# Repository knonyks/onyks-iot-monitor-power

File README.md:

## ESP32 power meter

Based on:

* ACS712 - 30A
* 2ma - 2ma voltage measuring transformer
* ADS1115 - I2C ADC 16bit

Programer:

* [ESP-prog](https://docs.espressif.com/projects/esp-iot-solution/en/latest/hw-reference/ESP-Prog_guide.html)

### PCB V1:

* [schematic](img/V1/schematic_v1.pdf)
* [bom](fab/V1/ibom.html)
* PCB

### PCB V2:

---

Author: Maciej Załęski [macmysz]

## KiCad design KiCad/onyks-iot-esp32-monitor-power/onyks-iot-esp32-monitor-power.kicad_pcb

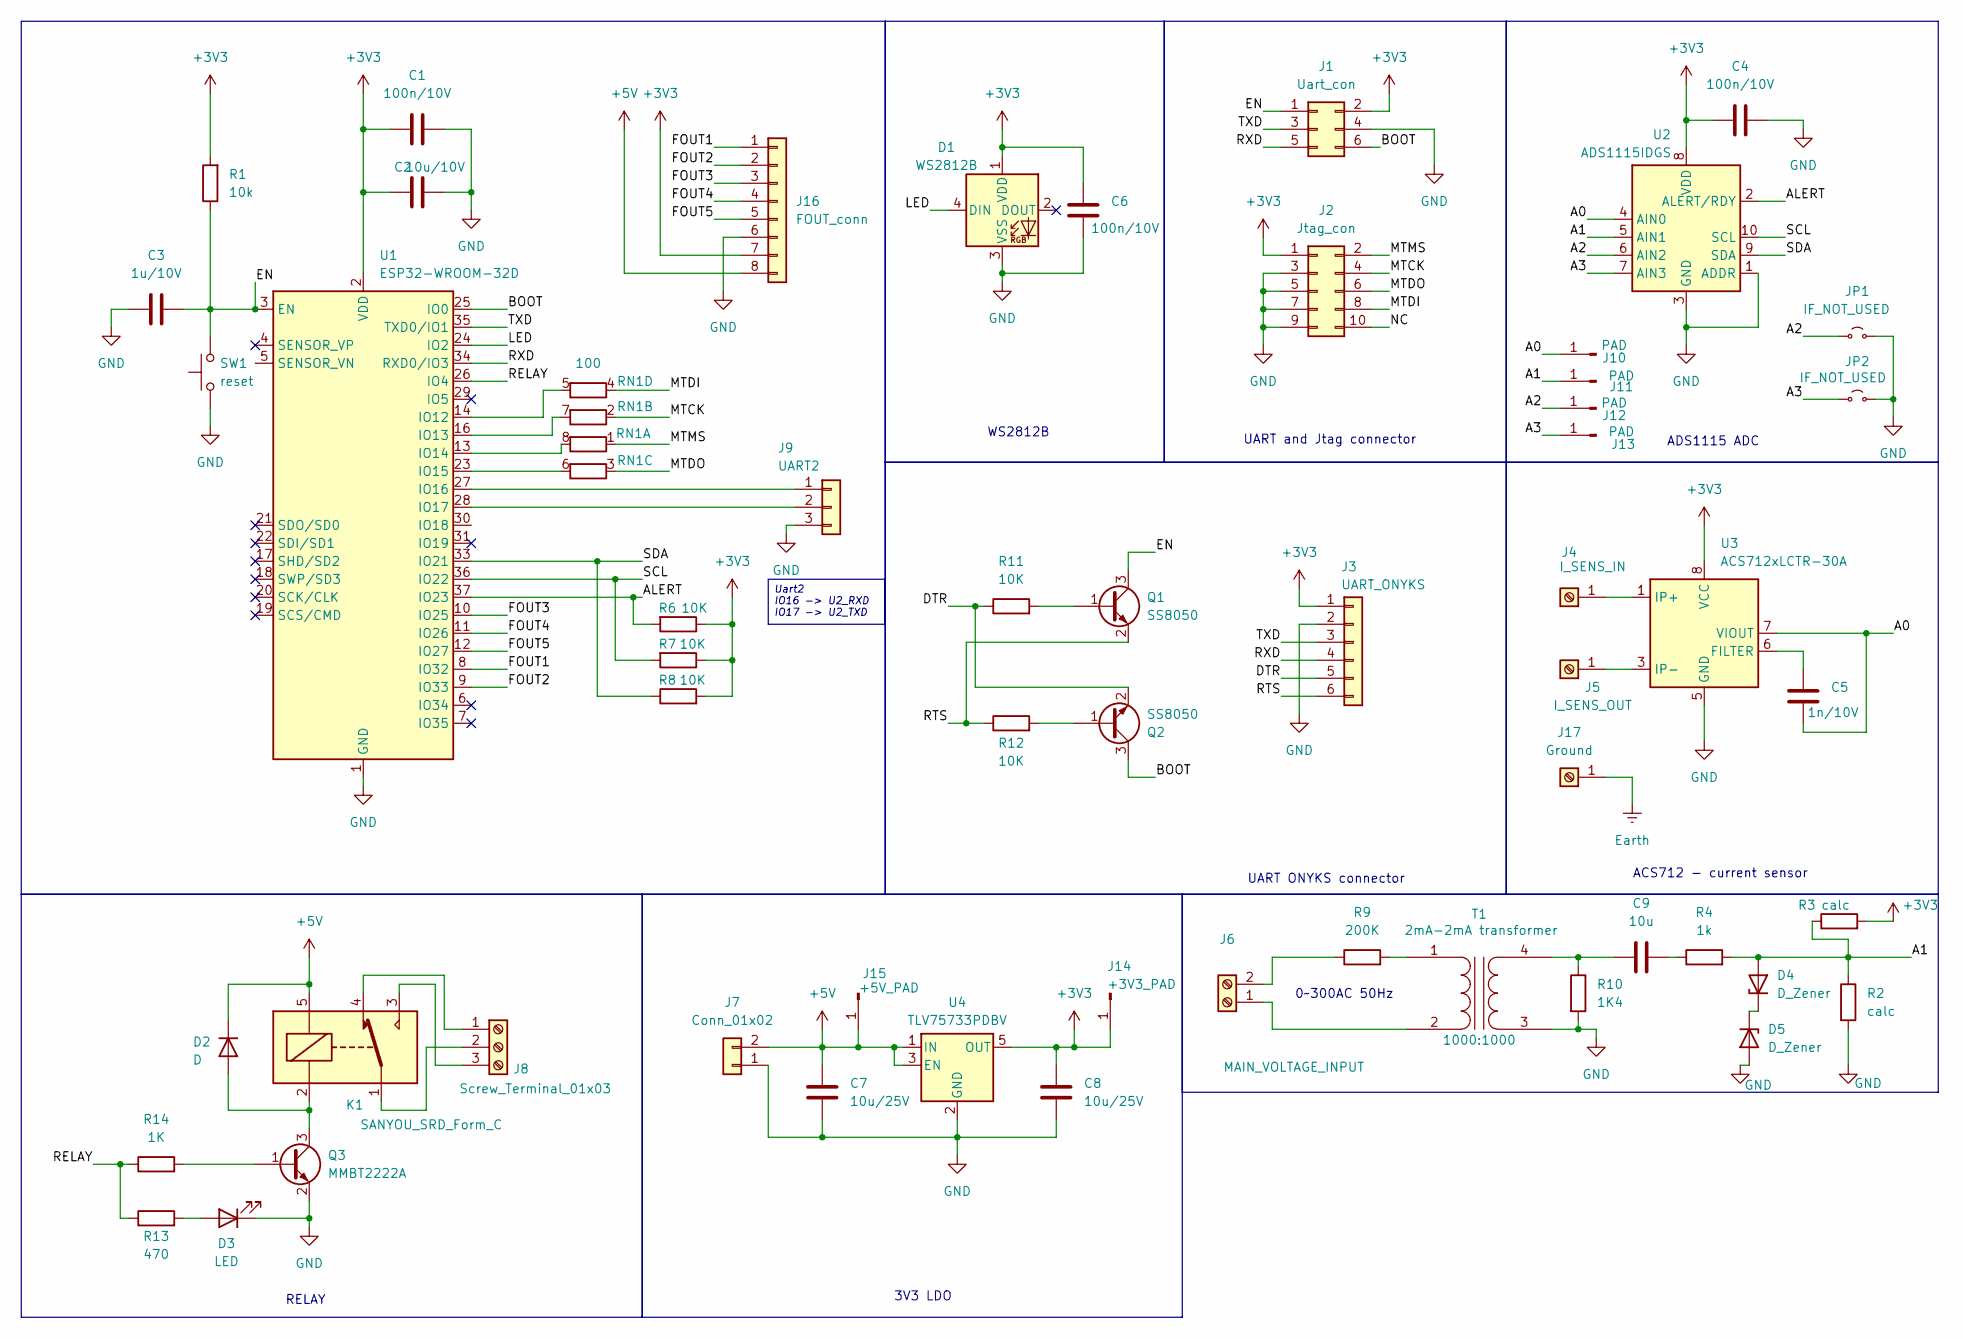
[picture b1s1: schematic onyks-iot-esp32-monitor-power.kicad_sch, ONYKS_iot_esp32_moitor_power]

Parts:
C1, C4, C6: 100n/10V; C_0805_2012Metric
C2: 10u/10V; C_0805_2012Metric
C3: 1u/10V; C_0805_2012Metric
C5: 1n/10V; C_0805_2012Metric
C7, C8: 10u/25V; C_0805_2012Metric
C9: 10u; C_0805_2012Metric
D1: WS2812B; LED_WS2812B_PLCC4_5.0x5.0mm_P3.2mm
D2: D; D_SMA
D3: LED; LED_0603_1608Metric
D4, D5: D_Zener; D_0805_2012Metric
J1: Uart_con; IDC-Header_2x03_P2.54mm_Vertical
J2: Jtag_con; IDC-Header_2x05_P2.54mm_Vertical
J3: UART_ONYKS; PinHeader_1x06_P2.54mm_Vertical
J4: I_SENS_IN; Screw Terminal M4 8x8
J5: I_SENS_OUT; Screw Terminal M4 8x8
J6: MAIN_VOLTAGE_INPUT; TerminalBlock_bornier-2_P5.08mm
J7: Conn_01x02; PinHeader_1x02_P2.54mm_Vertical
J8: Screw_Terminal_01x03; TerminalBlock_bornier-3_P5.08mm
J9: UART2; PinHeader_1x03_P2.54mm_Vertical
J10, J11, J12, J13: PAD; TestPoint_Pad_D1.0mm
J14: +3V3_PAD; TestPoint_Pad_D1.5mm
J15: +5V_PAD; TestPoint_Pad_D1.5mm
J16: FOUT_conn; PinSocket_1x08_P2.54mm_Vertical
J17: Ground; SolderWire-2sqmm_1x01_D2mm_OD3.9mm
JP1, JP2: IF_NOT_USED; SolderJumper-2_P1.3mm_Open_RoundedPad1.0x1.5mm
K1: SANYOU_SRD_Form_C; Relay_SPDT_SANYOU_SRD_Series_Form_C
Q1: SS8050; SOT-23-3
Q2: SS8050; SOT-23
Q3: MMBT2222A; SOT-23
R1: 10k; R_0805_2012Metric
R2, R3: calc; R_0805_2012Metric
R4: 1k; R_0805_2012Metric
R6, R7, R8, R11, R12: 10K; R_0805_2012Metric
R9: 200K; R_0805_2012Metric
R10: 1K4; R_0805_2012Metric
R13: 470; R_0805_2012Metric
R14: 1K; R_0805_2012Metric
RN1: 100; R_Array_Concave_4x0603
SW1: reset; SW_Tactile_SPST_NO_Straight_CK_PTS636Sx25SMTRLFS
T1: 2mA-2mA transformer; ZMPT101B
U1: ESP32-WROOM-32D
U2: ADS1115IDGS; TSSOP-10_3x3mm_P0.5mm
U3: ACS712xLCTR-30A; SOIC-8_3.9x4.9mm_P1.27mm
U4: TLV75733PDBV; SOT-23-5

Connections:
+3V3: C1.2, C2.1, C4.1, C6.1, C8.1, D1.1 (VDD), J1.2, J2.1, J3.1, J14.1, J16.7, R1.2, R3.2, R6.1, R7.1, R8.2, U1.2 (VDD), U2.8 (VDD), U3.8 (VCC), U4.5 (OUT)
+5V: C7.1, D2.1 (K), J7.2, J15.1, J16.8, K1.5, U4.1 (IN), U4.3 (EN)
/A0: C5.1, J10.1, U2.4 (AIN0), U3.7 (VIOUT)
/A1: D4.2 (A), J11.1, R2.1, R3.1, R4.2, U2.5 (AIN1)
/A2: J12.1, JP1.1 (A), U2.6 (AIN2)
/A3: J13.1, JP2.1 (A), U2.7 (AIN3)
/ALERT: R6.2, U1.37 (IO23), U2.2 (ALERT/RDY)
/BOOT: J1.6, Q2.3 (C), U1.25 (IO0)
/DTR: J3.5, Q2.2 (E), R11.1
/EN: C3.2, J1.1, Q1.3 (C), R1.1, SW1.2, U1.3 (EN)
/FOUT1: J16.1, U1.8 (IO32)
/FOUT2: J16.2, U1.9 (IO33)
/FOUT3: J16.3, U1.10 (IO25)
/FOUT4: J16.4, U1.11 (IO26)
/FOUT5: J16.5, U1.12 (IO27)
/LED: D1.4 (DIN), U1.24 (IO2)
/MTCK: J2.4, RN1.2 (R2.1)
/MTDI: J2.8, RN1.4 (R4.1)
/MTDO: J2.6, RN1.3 (R3.1)
/MTMS: J2.2, RN1.1 (R1.1)
/NC: J2.10
/RELAY: R13.1, R14.1, U1.26 (IO4)
/RTS: J3.6, Q1.2 (E), R12.1
/RXD: J1.5, J3.4, U1.34 (RXD0/IO3)
/SCL: R7.2, U1.36 (IO22), U2.10 (SCL)
/SDA: R8.1, U1.33 (IO21), U2.9 (SDA)
/TXD: J1.3, J3.3, U1.35 (TXD0/IO1)
Earth: J17.1
GND: C1.1, C2.2, C3.1, C4.2, C6.2, C7.2, C8.2, D1.3 (VSS), D3.1 (K), D5.2 (A), J1.4, J2.3, J2.5, J2.7, J2.9, J3.2, J7.1, J9.3, J16.6, JP1.2 (B), JP2.2 (B), Q3.2 (E), R2.2, R10.2, SW1.1, T1.3 (SA), U1.1 (GND), U1.15 (GND), U1.38 (GND), U1.39 (GND), U2.1 (ADDR), U2.3 (GND), U3.5 (GND), U4.2 (GND)
unnamed: C9.2, R4.1
unnamed: D2.2 (A), K1.2, Q3.3 (C)
unnamed: D3.2 (A), R13.2
unnamed: D4.1 (K), D5.1 (K)
unnamed: J4.1, U3.1 (IP+), U3.2 (IP+)
unnamed: J5.1, U3.3 (IP-), U3.4 (IP-)
unnamed: J6.1, T1.2 (AB)
unnamed: J6.2, R9.1
unnamed: J8.1, K1.4
unnamed: J8.2, K1.1
unnamed: J8.3, K1.3
unnamed: J9.1, U1.27 (IO16)
unnamed: J9.2, U1.28 (IO17)
unnamed: Q1.1 (B), R11.2
unnamed: Q2.1 (B), R12.2
unnamed: Q3.1 (B), R14.2
unnamed: RN1.8 (R1.2), U1.13 (IO14)
unnamed: RN1.7 (R2.2), U1.16 (IO13)
unnamed: RN1.6 (R3.2), U1.23 (IO15)
unnamed: RN1.5 (R4.2), U1.14 (IO12)
unnamed: R9.2, T1.1 (AA)
unnamed: C9.1, R10.1, T1.4 (SB)
unnamed: C5.2, U3.6 (FILTER)

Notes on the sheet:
ACS712 - current sensor
UART and Jtag connector
UART ONYKS connector
ADS1115 ADC
WS2812B
0~300AC 50Hz
3V3 LDO
RELAY
Uart2 IO16 -> U2_RXD IO17 -> U2_TXD

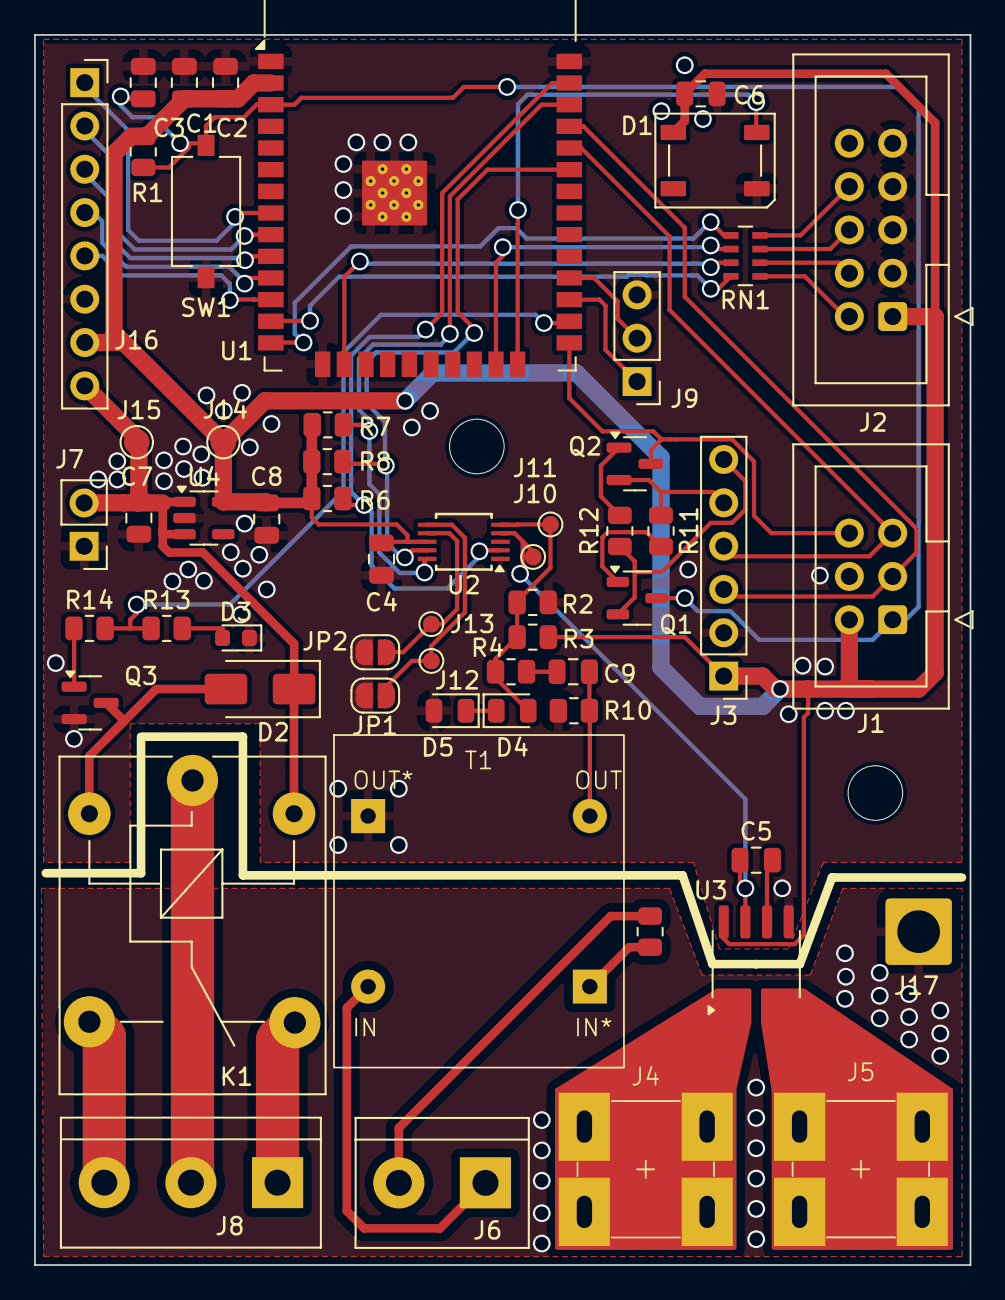
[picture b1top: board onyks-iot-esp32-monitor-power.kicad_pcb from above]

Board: 2 copper layers, 54.9 x 72.1 mm, 57 parts (0 on the bottom side), 50 nets.

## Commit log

2024-11-21 idea1
    list of elements to choose from and datasheets
2024-11-21 dodano folder docs
2024-11-21 usuniecie starych folderow
2024-11-21 add README.md
2024-11-21 add KiCad project
2024-12-02 update schemati
2024-12-02 Add ACS712 and ADS1115
2024-12-02 edit schemat
2024-12-02 edited docs
2024-12-08 scheme v1; Add fotprints
2024-12-08 update docs
2024-12-08 Add relay to sheme (not ended)
2024-12-09 Add relay and 5x extra free GPIO; sheme V1.1
2024-12-09 start editing pcb
2024-12-13 edit pcb
2024-12-15 pcb finished
2024-12-16 add Logo
2024-12-18 PCB update
2024-12-18 update PCB 2
2025-04-09 schemat errors fix_1
2025-04-23 doc V1
2025-04-23 edit readme
2025-04-23 add check list
2025-04-29 add sim
2025-04-29 work on sim1
2025-04-30 work on sim2
2025-05-02 sim change .md name
2025-05-02 add current sensor sim
2025-10-26 fab files v1
2025-11-02 vias 31mils
